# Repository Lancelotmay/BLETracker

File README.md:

# BLETracker

Copyright (C) 2026 Lancelot MEI

BLETracker is a Zephyr-based firmware project for a Bluetooth Low Energy tracker built around a Nordic nRF52840 platform and a u-blox SAM-M10 GNSS module. The repository also contains the associated board definition files and schematic design files.

## Overview

BLETracker is a portable external GNSS positioning device designed to work with a smartphone over BLE. It augments the phone’s built-in GNSS by offloading positioning to a dedicated low-power device.

Compared to relying solely on the phone, BLETracker focuses on delivering longer tracking duration and more stable positioning, while the phone remains the main interface for display, storage, and connectivity.

The system focuses on three practical goals:

- **Longer tracking time**: GNSS is handled by a dedicated device, reducing continuous GNSS load on the phone.
- **More stable positioning**: a standalone GNSS module with better antenna conditions can provide more consistent fixes during movement.
- **Simple integration**: location data is transmitted via BLE and can be consumed by a mobile app or logging system.

## Why this project

- Continuous GNSS on a phone drains battery quickly.
- Antenna constraints and device placement affect stability.
- Limited control over GNSS behavior for logging use cases.

BLETracker acts as an external GNSS sensor over BLE, offloading positioning while the phone handles UI and data.

## Design considerations

- **Low-power system design**: nRF52840 manages BLE communication and system control with efficient scheduling.
- **Dedicated GNSS module**: u-blox SAM-M10 is used for its power efficiency and reliable positioning performance.
- **Separation of concerns**: GNSS acquisition, BLE transport, and application logic are decoupled.
- **Portable form factor**: intended to be carried or attached during activity.

## Potential use cases

- Long-duration walking, hiking, or cycling with continuous track logging
- External GNSS receiver for mobile applications
- Lightweight positioning device for custom data collection
- Development platform for GNSS-related experiments

## Hardware

- Schematics and PCB design files are located under `hardware/` (KiCad sources).

## Repository layout

- `src/`: application firmware, BLE services, GNSS/UBX handling, and hardware glue.
- `boards/IMYTH/BLETracker/`: custom Zephyr board definition for the target hardware.
- `docs/`: project notes and design documents.
- `hardware/`: KiCad source files (converted from EasyCAD, need adjust) and related hardware assets.

## Build notes

This project is intended to be built with Zephyr and a configured Zephyr SDK / toolchain environment.

Typical build flow:

```sh
west build -b BLETracker/nrf52840
```

You may need to adjust the board target or workspace layout to match your local Zephyr setup.

## GitHub readiness notes

- `build/` and local editor state are intentionally ignored.
- `.vscode/` contains machine-local IDE configuration and is not required to build the project.
- `src/ubx_messages_header.h` is a generated u-blox header and retains its original upstream notice.

## License

Unless a file states otherwise, this repository is licensed under `GPL-2.0-only`. See [LICENSE](LICENSE).

Third-party or generated files may carry their own notices and should be treated according to the license text embedded in those files.

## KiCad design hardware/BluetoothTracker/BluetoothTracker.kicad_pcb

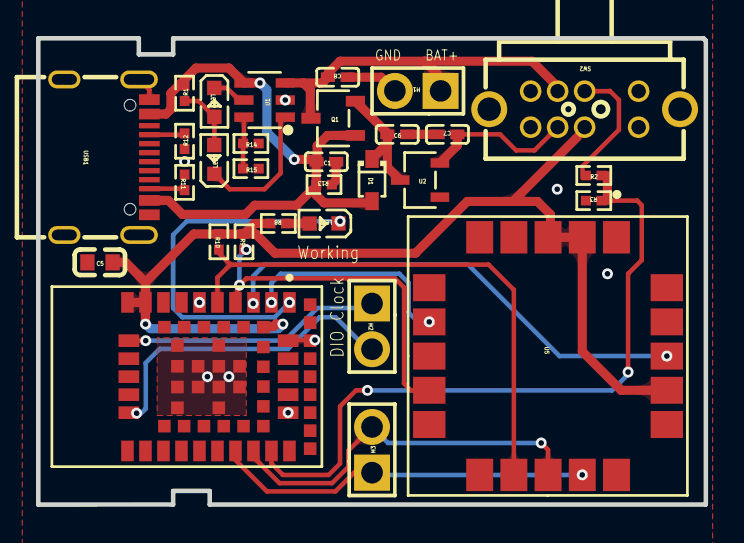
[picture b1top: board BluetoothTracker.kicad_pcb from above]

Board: 2 copper layers, 37.1 x 25.9 mm, 30 parts (0 on the bottom side), 26 nets.

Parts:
C1, C6, C7, C8: C0402
C5: C0603
D1: SOD-323_L1.8-W1.3-LS2.5-RD
H1, H2, H3: HDR-TH_2P-P2.54-V-M
LED4, LED7: LED0603-RD
LED6: LED0603-RD-YELLOW
Q1: SOT-23-3_L2.9-W1.6-P1.90-LS2.8-BR
R1, R2, R3, R8, R9, R10, R11, R12, R13, R14, R15: R0402
SW2: SW-TH_SSAC120200
U1: SOT-23-6_L2.9-W1.6-P0.95-LS2.8-BL
U2: SOT-23-3_L3.0-W1.7-P0.95-LS2.9-BR
U3: NINA_LGA67R_1500X1000X338_PIFA
U5: SAM-M8
USB1: USB-C-SMD_TYPE-C16PIN

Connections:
1PPS: U3.2, U5.7
3.3V: C5.2, R8.2, R9.1, R10.1, SW2.2, U3.9, U3.10, U3.31, U5.2, U5.3, U5.17
$1N2952: R11.2, USB1.B5
$1N2955: R12.2, USB1.A5
$1N6137: LED4.1, U1.1
$1N6365: LED4.2, LED7.2, R1.1
$1N6477: LED7.1, U1.5
$1N8277: C6.1, D1.1, Q1.2, U2.3
$1N11360: H2.1, U3.11
$1N11362: H2.2, U3.15
$1N22575: R2.1, SW2.6
$1N22590: C7.1, SW2.3, U2.2
$1N23834: LED6.2, R8.1
$1N24373: R14.1, R15.1, U1.6
BATT_ADC: R2.2, R3.1, U3.24
GND: C1.2, C5.1, C6.2, C7.2, C8.1, H1.2, R3.2, R11.1, R12.1, R13.1, R14.2, R15.2, U1.2, U2.1, U3.6, U3.12, U3.14, U3.26, U3.30, U3.53, U3.56, U3.57, U3.58, U3.59, U3.60, U3.61, U3.62, U3.63, U3.64, U3.65, U3.66, U3.67, U5.1, U5.4, U5.5, U5.6, U5.10, U5.11, U5.15, U5.16, U5.20, USB1.1, USB1.2, USB1.3, USB1.4, USB1.A1B12, USB1.B1A12
LED_M10: LED6.1, U3.1
M10_SCL: R10.2, U3.5, U5.12
M10_SDA: R9.2, U3.4, U5.9
N_RESET_M10: U3.3, U5.18
UART_M10_RXD: H3.1, U3.22, U5.14
UART_M10_TXD: H3.2, U3.23, U5.13
USB_D+: USB1.A6, USB1.B6
USB_D-: USB1.A7, USB1.B7
VBAT+: C8.2, H1.1, Q1.3, SW2.7, U1.3
VBUS_5V: C1.1, D1.2, Q1.1, R1.2, R13.2, U1.4, USB1.A4B9, USB1.B4A9

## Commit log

2026-02-28 init version, with BT adv and Battery ADC
2026-03-02 feat: add LNS (no test)
2026-03-03 Feat: LNS service
2026-03-25 First workable version
